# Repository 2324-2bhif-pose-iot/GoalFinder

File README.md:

# Goal Finder

IoT project in scope of POSE-PRPR and WLC, HTL Leonding, 2BHIF, JG 2324 in cooperation with Universität Wien.

## Introduction

When visually impaired people play basket ball, they need acoustic assistance for locating the basket and as feedback if the basket is hit.

For locating the basket, a constant beeping is sufficient. For a hit, a triumph fanfare may be played. Miss detection may result in an according tune.

Such assistance device may be directly mounted on the basket rack. They shall be easily mountable, e.g. by sliding them on the board or basket.

For hit detection, a short range laser distance sensor (ToF - time of flight sensor) is used. It is looking through the mesh of the basket and is therefore capable detecting a ball falling through the basket.

Optionally, hitting the basket-board may be detected using an acceleration sensor. When a ball hits the board or the ring, heavy motion can be expected and detected. If the ball does not pass the basket in time, a miss is detected.

The sensor device shall be controlled via a web application designed for mobile devices, to operate the system on the (basketball) field. The application may also assist in the game, for instance by automatically counting hits for multiple players.

## Project Goals

A basketball assistance device as described about shall be developed and deployed in the field.

## Hardware Platform

+ SoC: ESP32, see [Random Nerd Tutorials: ESP32- Pinout](https://randomnerdtutorials.com/esp32-pinout-reference-gpios/)
+ Distance Sensor: ToF sensor connected via I²C, such as VL53L0X. see [YouTube: ToF used with ESP32](https://www.youtube.com/watch?v=HeMlcCDYCEk).
+ Option: Acceleration sensor (TBD).
+ Audio: ESP32 DAC with external pre-amplifier, see [YouTube: ESP32 Audio: I2S & Built-In DACs Explained](https://www.youtube.com/watch?v=lgDu88Y411o)
+ Power supply: Grid via power adapter or power bank.

## Use Cases and User Stories

1. As a user, I want to control the device via web application on a smart phone as well as on a desktop PC.
1. As a player, I want the device to provide acoustic hints of the basket location.
1. As a player, I want the device to sound a triumph tune when the ball hits the basket.
1. As a player, it would be great to hear a sound when the ball hits the basket rack but not the basket.
1. As a user, I want to connect to the device via WiFi network that is spread by the device.
1. As a user, I want to integrate the device into my WiFi network easily.
1. As a user, I want that the device time is synchronized with the real time of my timezone.
1. As a user, I want to update the device software over the air.

## Tasks

This section describes the first task to be tackled on a high-level base.

1. Specify a roadmap / time table for the given tasks and user story implementation.
1. Develop a software design showing the major software components and their relations as well as required communication protocols.
1. Integrate a WiFi setup and configuration on the device.
1. Integrate a web server on the device.
1. Integrate an SNTP client on the device, including SNTP configuration via integrated web server.
1. Implement the SW-component to measure distances via distance senor.
1. Option: Implement SW-component to measure motion via motion sensor.
1. Implement hit / miss detection based on the measured values.
1. Implement audio output
1. Integrate suitable audio tracks for signalling events.
1. Option: Implement audio feedback via Bluetooth.
1. Implement a web front-end suitable for configuring the sensor device
1. Implement a web front-end for game play.
1. Integrate and enable SWUOTA (software update over the air).

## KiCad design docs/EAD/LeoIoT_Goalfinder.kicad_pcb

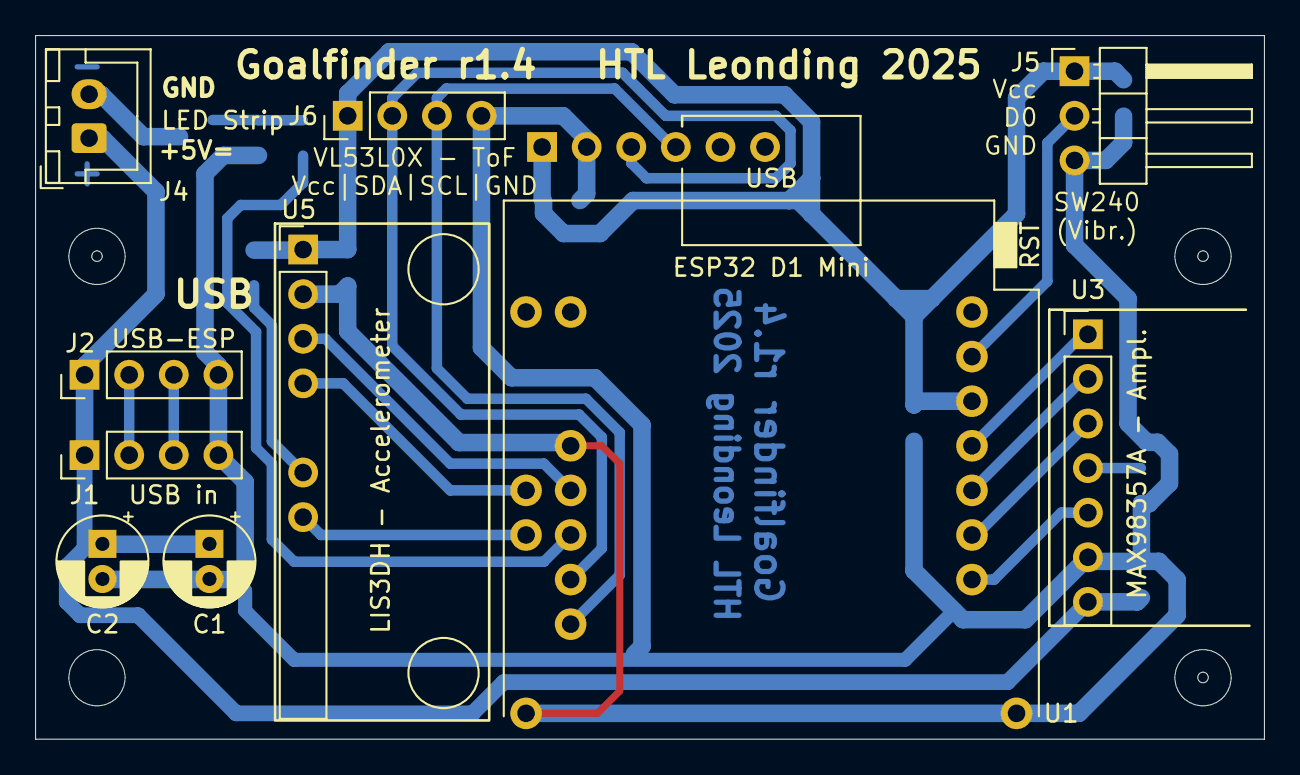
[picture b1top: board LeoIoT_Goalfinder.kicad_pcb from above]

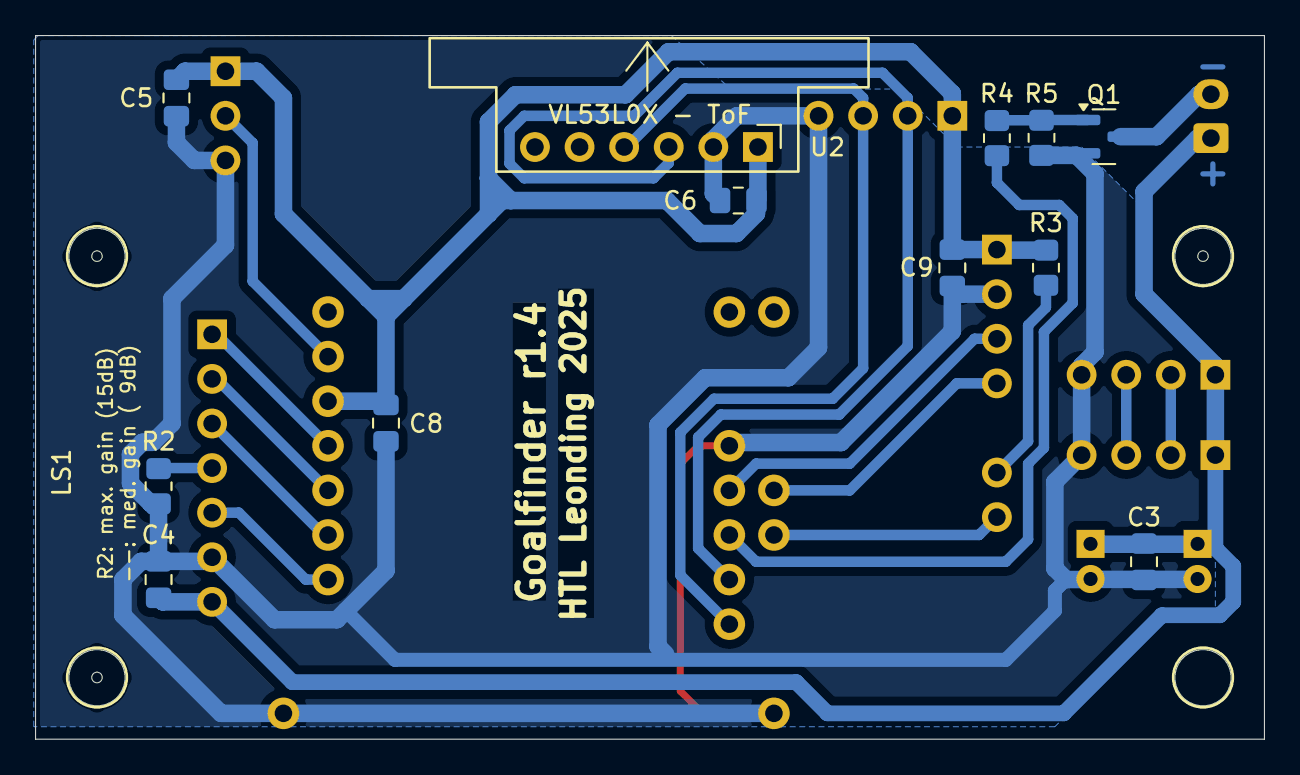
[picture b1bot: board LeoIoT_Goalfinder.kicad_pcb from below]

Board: 2 copper layers, 70.0 x 40.1 mm, 27 parts (13 on the bottom side), 20 nets.

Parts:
C1: 22µF; CP_Radial_D5.0mm_P2.00mm
C2: 4,7µF; CP_Radial_D5.0mm_P2.00mm
C3, C4, C5, C6, C8, C9: 100nF; C_0805_2012Metric_Pad1.18x1.45mm_HandSolder
J1: USB in; PinHeader_1x04_P2.54mm_Vertical
J2: USB-ESP; PinHeader_1x04_P2.54mm_Vertical
J4: LED Strip; JST_XH_B2B-XH-A_1x02_P2.50mm_Vertical
J5: SW240 - Vcc/D0/GND; PinHeader_1x03_P2.54mm_Horizontal
J6: VL53L0X-ToF Vcc/SDA/SCL/GND; PinHeader_1x04_P2.54mm_Vertical
LS1: Speaker; Mono-Enclosed_Speaker_70x30x17mm_onboard
MH1, MH2, MH3, MH4: MountingHole_3.2mm_M3
Q1: IRLML2502; SOT-23
R2, R3: 100k; R_0805_2012Metric_Pad1.20x1.40mm_HandSolder
R4: 1k; R_0805_2012Metric_Pad1.20x1.40mm_HandSolder
R5: 33k; R_0805_2012Metric_Pad1.20x1.40mm_HandSolder
U1: ESP32 D1 Mini; ESP32_D1_mini
U2: VL53L0X - ToF; VL53L0X_Breakout_Board_vertical_flat
U3: MAX98357A - Ampl.; MAX98357A_Breakout_Board
U5: LIS3DH - Accelerometer; LIS3DH_Breakout_Board

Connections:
3V3: C5.1, C6.1, C8.1, C9.1, J5.1, J6.1, R3.1, U1.16 (3V3), U2.1 (VCC), U5.1 (VCC)
5V: C1.1, C2.1, C3.1, C4.1, J1.1, J2.1, J4.1, U3.7 (VDD)
/LED_PWR: J4.2, Q1.3 (D)
GND: C1.2, C2.2, C3.2, C4.2, C5.2, C6.2, C8.2, C9.2, J1.4, J2.4, J5.3, J6.4, Q1.2 (S), R2.1, R5.2, U1.1 (GND), U1.22 (GND), U1.33 (GND), U2.2 (GND), U3.6 (GND), U5.2 (GND)
unnamed: J1.2, J2.2
unnamed: J1.3, J2.3
unnamed: J5.2, U1.18 (IO_13/TCK)
unnamed: J6.2, U1.27 (IO_21/SDA_1), U2.3 (SDA)
unnamed: J6.3, U1.25 (IO_22/SCL_1), U2.4 (SCL)
unnamed: Q1.1 (G), R4.2, R5.1
unnamed: U1.32 (IO_04), U5.4 (SDA/SDI/SDO)
unnamed: U1.14 (IO_05/SS), U3.1 (LRCLK)
unnamed: U1.30 (IO_12/TDI), U5.7 (INT1)
unnamed: U1.31 (IO_16/U2_RX), U5.3 (SCL/SPC)
unnamed: R4.1, U1.29 (IO_17/U2_TXC)
unnamed: U1.8 (IO_18/CLK), U3.5 (~SD_MODE)
unnamed: U1.10 (IO_19/MISO), U3.3 (DIN)
unnamed: U1.12 (IO_23/MOSI), U3.2 (BCLK)
unnamed: R2.2, U3.4 (GAIN_SLOT)
unnamed: R3.2, U5.6 (CS)

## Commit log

2024-02-23 initial project description
2024-02-29 Init
2024-03-05 Created project
2024-03-05 Changed framework to arduino
2024-03-07 I added system specifications
2024-03-10 added docs
2024-03-12 Added pin configuration
2024-03-12 Added image of pin configuration
2024-03-12 updated project plan
2024-03-12 updated src
2024-03-12 added wifi
2024-03-14 Updated pin configuration
2024-03-14 Removed file
2024-03-21 Included libraries
2024-03-25 included libs after moving them in new folders
2024-03-25 added schematic moved 3pty docs to infrastructure repo
2024-04-02 Adjusted platformio.ini
2024-04-04 moved libs & singleton, created gfApp
2024-04-04 Made library for tof sensor
2024-04-09 finished vibrationsensor
2024-04-09 Added Audioplayer test
2024-04-16 test
2024-04-16 Cleaned app
2024-04-22 Added webserver, webapp, filesystem
2024-04-22 Renamed webapp folder
2024-04-23 Edited Projekt Plan
2024-04-23 added games view and gamelistitem component
2024-04-23 added add params to vue component
2024-04-25 Added tests
2024-04-25 added output to tof sensor
2024-04-30 added destructors
2024-05-02 added bt lib in libs_extra
2024-05-06 Updated webapp
2024-05-07 Updated AudioPlayer for I2S output
2024-05-07 Updated Tofsensor lib
2024-05-21 did Vibrationssensor
2024-05-21 Uncommented
2024-05-21 fixed application
2024-05-21 added basketball shot tracker
2024-05-23 added sensitivity of vibrationsensor to web app
2024-05-26 updated schematic added PCB views
2024-05-26 added KiCAD sources
2024-05-27 updated PCB layout (extended wire width)
2024-05-28 finished PCB introduced housing
2024-05-28 Added some translations to web app
2024-05-28 added power support capacities, updated schematic and PCB to r1.1
2024-05-31 improved HW: - added capacitors for each breakout board - made GND lines wider and added GND shield areas - added HW revision 01.02 added technical drawings for case factoring
2024-05-31 updated gitignore
2024-06-03 updated PCB r 01.02
2024-06-04 Updated application
2024-06-04 made led fade
2024-06-04 Added new sounds
2024-06-04 Built webapp
2024-06-05 Added more translations to the webapp
2024-06-06 Dist package
2024-06-06 Edited index
2024-06-13 Implemented OTA
2024-06-13 added buttons instead of slider in webapp
2024-06-13 added application
2024-06-13 del WLAN
2024-06-13 Updated app
2024-06-18 Added get server request
2024-06-18 added settings class and HandleLoadSettings function
2024-06-18 Fixed webserver
2024-06-18 added metronomsound
2024-06-18 added led
2024-06-18 added leaderboard
2024-06-18 updated webapp and application
2024-06-19 Fixed LED Controller
2024-06-19 Added post http request
2024-06-19 added 4 LED-Modus, LED Vue
2024-06-19 Edited about page
2024-06-19 Fixed file paths
2024-06-19 made LED Controller compilable fixed constants in App AppGoalfinder: moved constants and instances into class scope replaced sound clips added sound clip fond added 3D models for mounting poles
2024-06-19 Adjusted about page
2024-06-19 added SwuOTA page sample
2024-06-19 SSID validation, deleted PW
2024-06-19 integrated LedController fixed LedController
2024-06-19 i added a german translation
2024-06-19 added c-tor, d-tor
2024-06-19 added c-tor ledChannel
2024-06-19 Added validation
2024-06-19 finished LedController
2024-06-19 made settings persistence aware
2024-06-19 implemented settings.h and gave members value in .cpp
2024-06-19 added Settings.cpp
2024-06-19 integrated settings to app -> web server need to be adjusted refactored app regarding sound playback
2024-06-19 added 'clearModifiedState"
2024-06-19 finished translation to german
2024-06-19 implemented settings class
2024-06-19 Updated Webserver to use new Settings
2024-06-19 Changed condition
2024-06-19 refactored event and announcement processing
2024-06-19 updated ignore list
2024-06-19 Adjusted settings page
2024-06-19 modified settings
2024-06-19 Edited webapp
2024-06-19 Added try and catch in webapp
2024-06-19 added method declaration for setting the sensitivity
2024-06-19 modified setDeviceName
2024-06-19 implemented ledmode in settings
2024-06-19 added sensitivity (not completely done)
2024-06-19 added off button in LED Modes
2024-06-19 fixed sound introduced and applied settings added metronome
2024-06-19 updated mounting poles
2024-06-20 added logos
2024-06-23 Added load settings and edited about page
2024-06-23 Added load settings
2024-07-01 updated distance pole models
2024-10-04 fixed timing / scheduling of different functional blocks partial code cleanup added TODOs and comments for further versions removed OTA because no suitable library is available anymore improved sound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
2024-10-14 improved graphics added intropage
2024-11-04 Redid webapp
2024-12-10 Updated webapp deps
2024-12-11 Refined design and PCB layout and added BOM - added SMD resistors - shaped PCB prints
2025-01-08 #1 Added power button in webapp
2025-01-10 Create automated firmware build
2025-01-14 Flash Instruction
2025-01-16 Feature #1 implemented
2025-01-22 bluetooth button
2025-01-22 Updated getting started and automatic build scripts
2025-01-27 Updated Job Title
    to try if job has sufficient permissions
2025-01-27 added write permissions to content for creating releases
2025-01-27 adjusted build and release workflow permissions
2025-01-29 updated BOM
2025-03-04 Fixed play/stop button #1
2025-03-05 improved rest api end points
2025-03-09 Started implementation for automatic shot and hit detection
2025-03-10 Created game model and ui for shot challenge
2025-03-10 finished automatic hit and miss detection
2025-03-10 fixed typo
2025-03-10 Improved api endpoints
2025-03-10 Bug fixes
2025-03-11 added multi-threading
2025-03-18 update webapp (detec miss/hit and get to the next p, start/stop btn)
2025-05-03 added schematic and PCBs for r1.3
2025-06-09 Added register, start and stop endpoints for GoalFinderHub
2025-06-13 added r1.4 of PCB and SMD-only PCB layout as well as production files
2025-06-13 finalized Goalfinder r1.4 + added optional accelerometer + added solder pads / pins for external USB socket and USB plug to ESP32 + added 'compact' variant with only SMD components + created producti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
2025-06-16 update Goalfinder Case with back-mount options
2025-06-19 Added printable model for powerbank holder for Anker 10Ah powerbanks
2025-06-19 added 3mf files to gitignore
2025-06-22 Communication with GoalFinderHub, Small fixes
2025-08-11 updated schematics
2025-09-14 restructured projects
2025-09-14 frontend for lidar sensor detection distance
2025-09-17 updated goalfinder case zu rev 1.1
2025-09-24 hit detection distance configurable, compressed webapp
2025-09-24 dont detect vibration when audio is playing
2025-09-24 new version
2025-10-03 added hit and miss sound configuration
2025-10-05 new challenge added
2025-10-05 Added sound clip selection
2025-10-05 removed audio playing check in detection
2025-10-07 Added translations and description of gamemodes
2025-10-14 fix detection
2025-10-14 improved webapp
2025-10-17 adjusted cases
2025-10-17 added case plates with openings (and logo)
